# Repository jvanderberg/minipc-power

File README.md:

# minipc-power

Small power board for MCU-based emulator builds (Pico / ESP32 class with a 12 V 5" LCD). Runs from USB-C or a 1S2P
18650 pack, charges the pack whenever USB-C is plugged in, and supplies 12 V, 5 V and 3.3 V.

## Features

- **USB-C PD input:** requests 9 V (CH224Q), falls back to 5 V on non-PD chargers; TVS on VBUS.
- **Charger:** BQ25606 standalone switching charger, 1.44 A charge to 4.2 V, 1.9 A input limit. Power path: the
  board runs from USB even with a dead or missing pack. NTC input for charge-temperature limits.
- **Battery protection** for bare cells: HY2113 protector (over-charge 4.28 V, over-discharge 2.80 V, over-current,
  short circuit), 10 A fuse, reverse-polarity FET.
- **Outputs**, all switched together by one on/off switch (off by default):
  - **12 V, 0.5 A:** TPS61178 synchronous boost with output disconnect (for the LCD)
  - **5 V, 2.5 A:** TPS61088-Q1 synchronous boost with a soft-start load switch
  - **3.3 V, 1.5 A:** TPS63802 buck-boost (regulated across the whole battery range)
- **Power budget:** 15 W combined as a peak; about 10-12 W continuous in a closed box (see `docs/thermal.md`).
- **Solder pads** for everything: battery, outputs, on/off switch, NTC, status (charging, power good, 3.3 V good,
  battery voltage sense).
- **Board:** 52 x 36 mm, 4 layers (JLCPCB JLC04161H-7628), parts from LCSC; every part has its datasheet link.

## Status

Design reviewed, not yet built. Bench checks to run first: `docs/power-design.md` s9 and `docs/review-2026-10-24.md`.
`hardware/production/` predates the latest board changes: regenerate it before ordering.

## Files

- `hardware/` - KiCad 10 project (schematic, board, symbols, footprints, 3D models)
- `tools/` - the schematic and board are generated by these scripts; edit them, not the KiCad files:
  `python3 tools/gen_schematic.py && bash tools/build_board.sh` (needs KiCad 10 and
  [kicad-skills](https://github.com/jvanderberg/kicad-skills))
- `docs/requirements.md` - requirements and architecture (start here)
- `docs/power-design.md` - every component value and where it comes from
- `docs/thermal.md` - heat budget
- `docs/review-2026-10-24.md` - design review: fixed, open, owner decisions, bench checks
- `docs/layout-compliance.md` - each converter's layout against its datasheet
- `docs/skill-gaps.md` - problems found in the kicad-skills plugin while designing this board

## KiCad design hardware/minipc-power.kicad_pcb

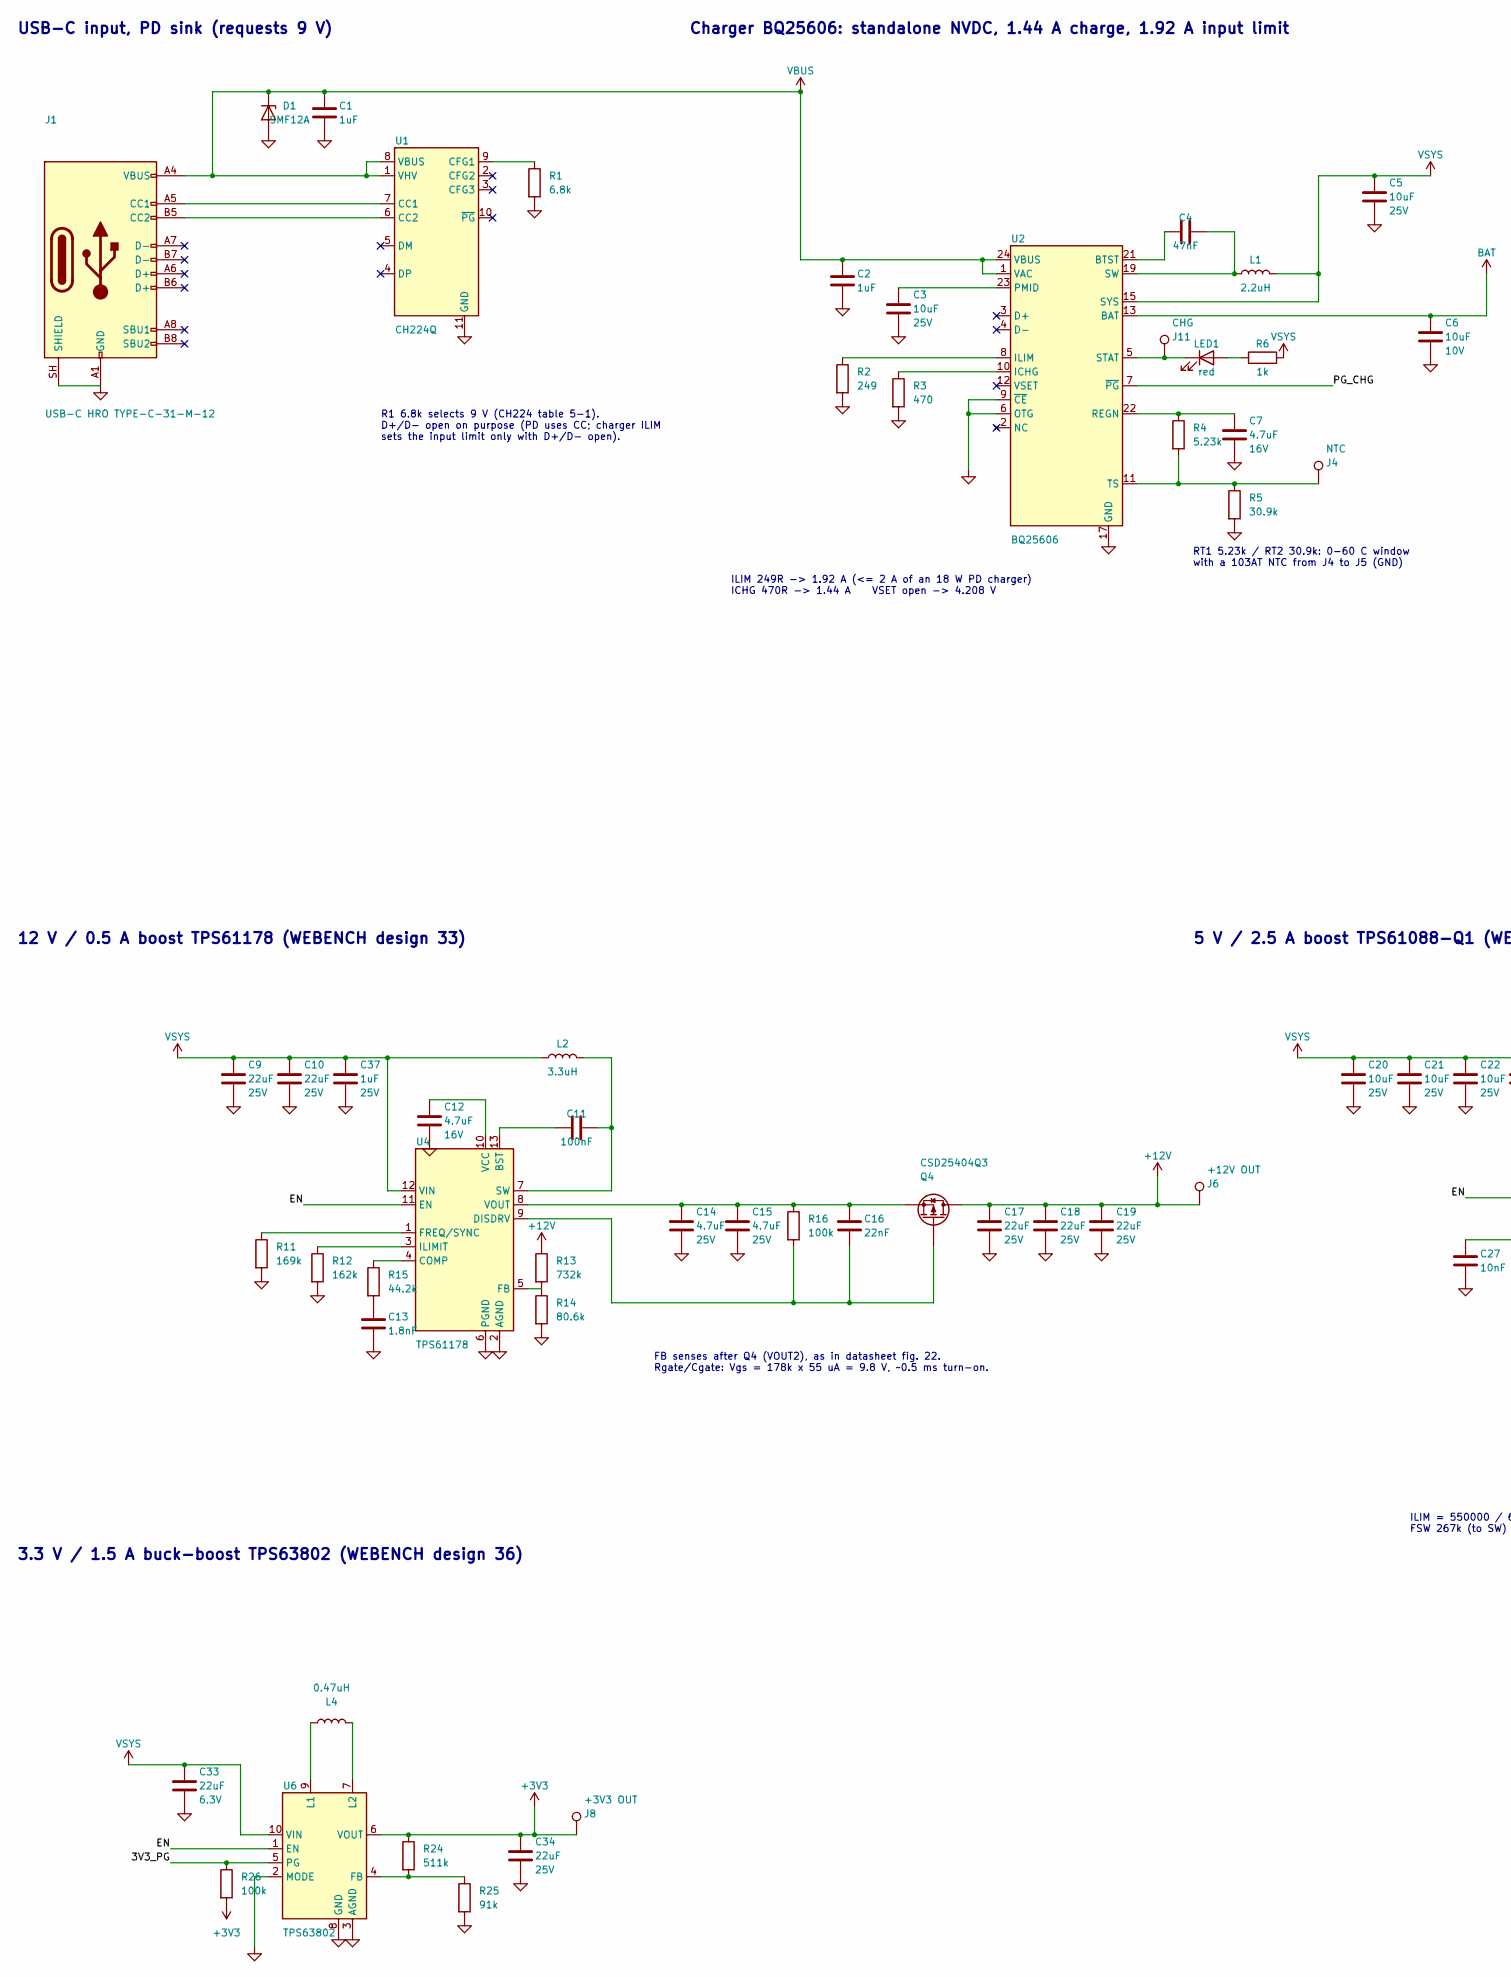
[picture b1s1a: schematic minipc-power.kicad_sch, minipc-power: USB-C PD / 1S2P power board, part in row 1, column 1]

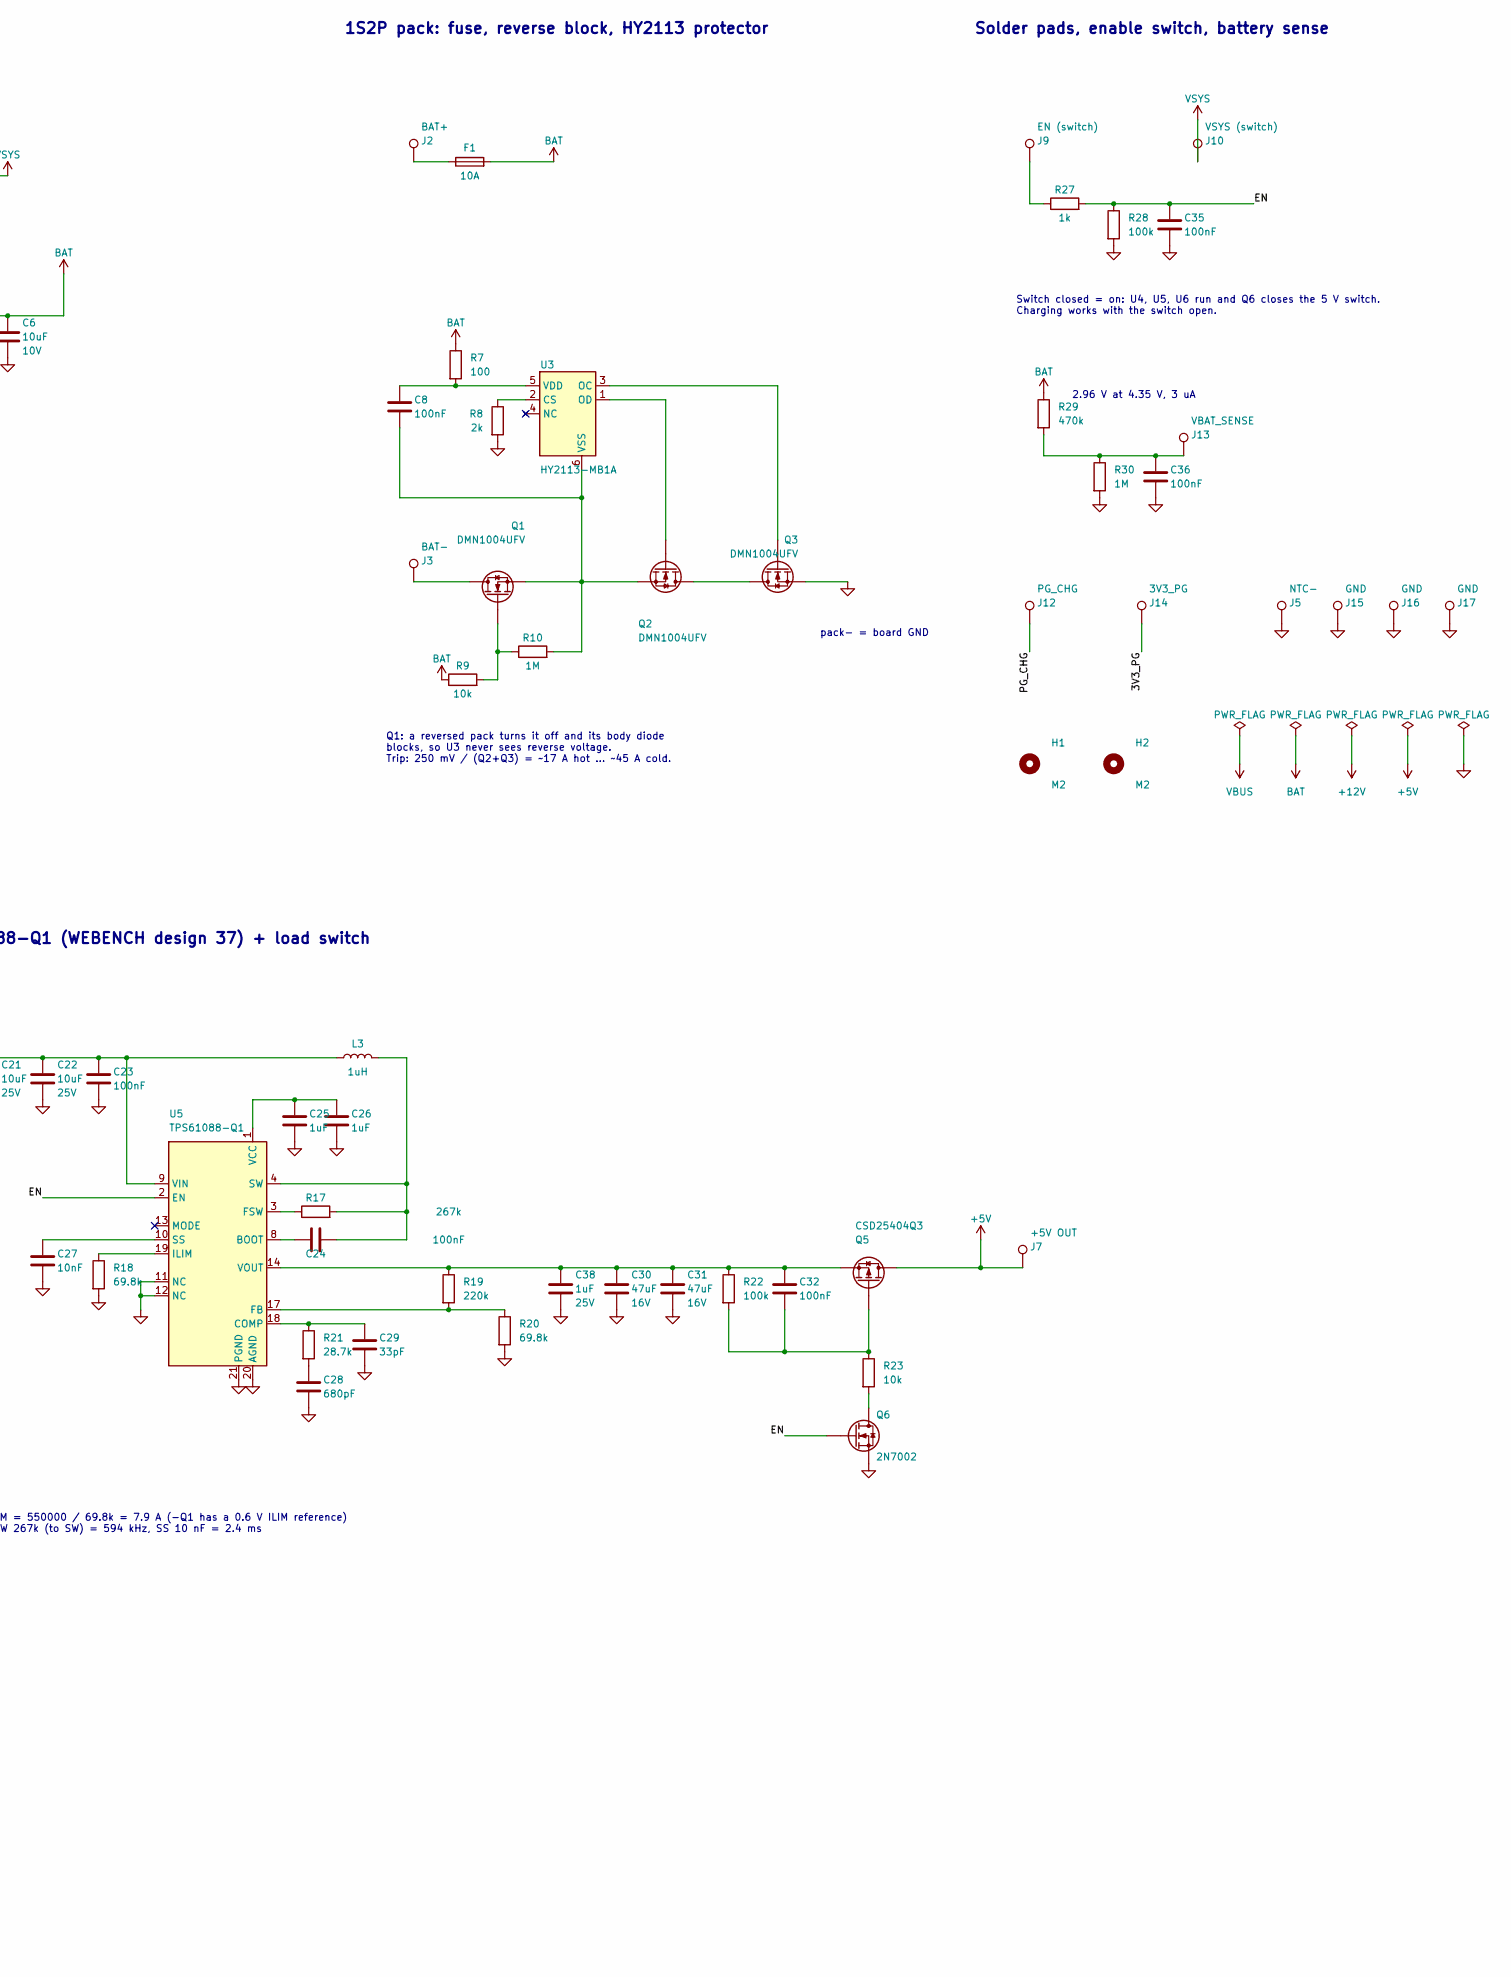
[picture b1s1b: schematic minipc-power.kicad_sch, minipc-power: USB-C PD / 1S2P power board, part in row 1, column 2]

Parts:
C1, C2, C25, C26: 1uF; C_0603_1608Metric; LCSC C15849
C3, C5, C20, C21, C22: 10uF; C_0805_2012Metric; Voltage 25V; LCSC C15850
C4: 47nF; C_0402_1005Metric; LCSC C307434
C6: 10uF; C_0603_1608Metric; Voltage 10V; LCSC C19702
C7, C12: 4.7uF; C_0603_1608Metric; Voltage 16V; LCSC C19666
C8, C11, C23, C24, C32, C35, C36: 100nF; C_0402_1005Metric; LCSC C1525
C9, C10, C34: 22uF; C_0805_2012Metric; Voltage 25V; LCSC C45783
C13: 1.8nF; C_0402_1005Metric; LCSC C107024
C14, C15: 4.7uF; C_0805_2012Metric; Voltage 25V; LCSC C1779
C16: 22nF; C_0402_1005Metric; LCSC C337699
C17, C18, C19: 22uF; C_1210_3225Metric; Voltage 25V; LCSC C52306
C27: 10nF; C_0402_1005Metric; LCSC C15195
C28: 680pF; C_0402_1005Metric; LCSC C307451
C29: 33pF; C_0402_1005Metric; LCSC C70465
C30, C31: 47uF; C_1210_3225Metric; Voltage 16V; LCSC C77101
C33: 22uF; C_0603_1608Metric; Voltage 6.3V; LCSC C59461
C37, C38: 1uF; C_0402_1005Metric; Voltage 25V; LCSC C52923
D1: SMF12A; D_SOD-123F; LCSC C123800
F1: 10A; Fuse_Littelfuse-NANO2-451_453; LCSC C44479
H1, H2: M2; MountingHole_2.2mm_M2
J1: USB-C HRO TYPE-C-31-M-12; USB_C_Receptacle_HRO_TYPE-C-31-M-12; LCSC C165948
J2: BAT+; TestPoint_THTPad_2.5x2.5mm_Drill1.2mm
J3: BAT-; TestPoint_THTPad_D2.5mm_Drill1.2mm
J4: NTC; TestPoint_THTPad_2.0x2.0mm_Drill1.0mm
J5: NTC-; TestPoint_THTPad_D2.0mm_Drill1.0mm
J6: +12V OUT; TestPoint_THTPad_2.5x2.5mm_Drill1.2mm
J7: +5V OUT; TestPoint_THTPad_2.5x2.5mm_Drill1.2mm
J8: +3V3 OUT; TestPoint_THTPad_2.5x2.5mm_Drill1.2mm
J9: EN (switch); TestPoint_THTPad_2.0x2.0mm_Drill1.0mm
J10: VSYS (switch); TestPoint_THTPad_2.0x2.0mm_Drill1.0mm
J11: CHG; TestPoint_THTPad_2.0x2.0mm_Drill1.0mm
J12: PG_CHG; TestPoint_THTPad_2.0x2.0mm_Drill1.0mm
J13: VBAT_SENSE; TestPoint_THTPad_2.0x2.0mm_Drill1.0mm
J14: 3V3_PG; TestPoint_THTPad_2.0x2.0mm_Drill1.0mm
J15, J16, J17: GND; TestPoint_THTPad_D2.5mm_Drill1.2mm
L1: 2.2uH; FXL0630-2R2-M; LCSC C167218
L2: 3.3uH; FXL0630-3R3-M; LCSC C167219
L3: 1uH; FXL0630-1R0-M; LCSC C167216
L4: 0.47uH; FXL0530-R47-M; LCSC C475515
LED1: red; LED_0603_1608Metric; LCSC C2286
Q1, Q2, Q3: DMN1004UFV; Diodes_PowerDI3333-8; LCSC C316138
Q4, Q5: CSD25404Q3; VSON-8_3.3x3.3mm_P0.65mm_NexFET; LCSC C2865523
Q6: 2N7002; SOT-23; LCSC C8545
R1: 6.8k; R_0402_1005Metric; LCSC C25917
R2: 249; R_0402_1005Metric; LCSC C25096
R3: 470; R_0402_1005Metric; LCSC C25117
R4: 5.23k; R_0402_1005Metric; LCSC C25907
R5: 30.9k; R_0402_1005Metric; LCSC C270615
R6, R27: 1k; R_0402_1005Metric; LCSC C11702
R7: 100; R_0402_1005Metric; LCSC C25076
R8: 2k; R_0402_1005Metric; LCSC C4109
R9, R23: 10k; R_0402_1005Metric; LCSC C25744
R10, R30: 1M; R_0402_1005Metric; LCSC C26083
R11: 169k; R_0402_1005Metric; LCSC C25758
R12: 162k; R_0402_1005Metric; LCSC C54068
R13: 732k; R_0402_1005Metric; LCSC C27016
R14: 80.6k; R_0402_1005Metric; LCSC C25921
R15: 44.2k; R_0402_1005Metric; LCSC C25895
R16, R22, R26, R28: 100k; R_0402_1005Metric; LCSC C25741
R17: 267k; R_0402_1005Metric; LCSC C270622
R18, R20: 69.8k; R_0402_1005Metric; LCSC C26985
R19: 220k; R_0402_1005Metric; LCSC C25767
R21: 28.7k; R_0402_1005Metric; LCSC C26972
R24: 511k; R_0402_1005Metric; LCSC C64042
R25: 91k; R_0402_1005Metric; LCSC C144733
R29: 470k; R_0402_1005Metric; LCSC C25790
U1: CH224Q; CH224Q_C46061833; LCSC C46061833
U2: BQ25606; Texas_RGE0024H_VQFN-24-1EP_4x4mm_P0.5mm_EP2.7x2.7mm_Thermal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; LCSC C374063
U3: HY2113-MB1A; SOT-23-6; LCSC C168772
U4: TPS61178; TPS61178RNWR; LCSC C127918
U5: TPS61088-Q1; Texas_VQFN-RHL-20_ThermalVias; LCSC C1850341
U6: TPS63802; TPS63802DLAR; LCSC C2845237

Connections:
+3V3: C34.1, J8.1, R24.1, R26.2, U6.6 (VOUT)
+5V: J7.1, Q5.1 (D), Q5.2 (D), Q5.3 (D)
+12V: C17.1, C18.1, C19.1, J6.1, Q4.1 (D), Q4.2 (D), Q4.3 (D), R13.1
/3V3_PG: J14.1, R26.1, U6.5 (PG)
/EN: C35.1, Q6.1 (G), R27.2, R28.1, U4.11 (EN), U5.2 (EN), U6.1 (EN)
/PG_CHG: J12.1, U2.7 (~PG)
BAT: C6.1, F1.2, R7.1, R9.1, R29.1, U2.13 (BAT), U2.14 (BAT)
GND: C1.2, C2.2, C3.2, C5.2, C6.2, C7.2, C9.2, C10.2, C12.2, C13.2, C14.2, C15.2, C17.2, C18.2, C19.2, C20.2, C21.2, C22.2, C23.2, C25.2, C26.2, C27.2, C28.2, C29.2, C30.2, C31.2, C33.2, C34.2, C35.2, C36.2, C37.2, C38.2, D1.2 (A), J1.A1 (GND), J1.A12 (GND), J1.B1 (GND), J1.B12 (GND), J1.SH (SHIELD), J5.1, J15.1, J16.1, J17.1, Q3.1 (S), Q3.2 (S), Q3.3 (S), Q6.2 (S), R1.2, R2.2, R3.2, R5.2, R8.2, R11.2, R12.2, R14.2, R18.2, R20.2, R25.2, R28.2, R30.2, U1.11 (GND), U2.6 (OTG), U2.9 (~CE), U2.17 (GND), U2.18 (GND), U2.25 (GND), U4.2 (AGND), U4.6 (PGND), U5.11 (NC), U5.12 (NC), U5.20 (AGND), U5.21 (PGND), U6.2 (MODE), U6.3 (AGND), U6.8 (GND)
unnamed: C4.2, L1.1, U2.19 (SW), U2.20 (SW)
unnamed: C13.1, R15.2
unnamed: C24.2, L3.2, R17.2, U5.4 (SW), U5.5 (SW), U5.6 (SW), U5.7 (SW)
unnamed: C28.1, R21.2
unnamed: C36.1, J13.1, R29.2, R30.1
unnamed: F1.1, J2.1
unnamed: J1.A5 (CC1), U1.7 (CC1)
unnamed: J1.B5 (CC2), U1.6 (CC2)
unnamed: J9.1, R27.1
unnamed: LED1.2 (A), R6.1
unnamed: J11.1, LED1.1 (K), U2.5 (STAT)
unnamed: J3.1, Q1.5 (D)
unnamed: Q1.4 (G), R9.2, R10.1
unnamed: Q2.5 (D), Q3.5 (D)
unnamed: Q2.4 (G), U3.1 (OD)
unnamed: Q3.4 (G), U3.3 (OC)
unnamed: C16.2, Q4.4 (G), R16.2, U4.9 (DISDRV)
unnamed: C14.1, C15.1, C16.1, Q4.5 (S), R16.1, U4.8 (VOUT)
unnamed: C32.2, Q5.4 (G), R22.2, R23.1
unnamed: C30.1, C31.1, C32.1, C38.1, Q5.5 (S), R19.1, R22.1, U5.14 (VOUT), U5.15 (VOUT), U5.16 (VOUT)
unnamed: Q6.3 (D), R23.2
unnamed: R1.1, U1.9 (CFG1)
unnamed: C4.1, U2.21 (BTST)
unnamed: R3.1, U2.10 (ICHG)
unnamed: R2.1, U2.8 (ILIM)
unnamed: C3.1, U2.23 (PMID)
unnamed: C7.1, R4.1, U2.22 (REGN)
unnamed: J4.1, R4.2, R5.1, U2.11 (TS)
unnamed: R8.1, U3.2 (CS)
unnamed: C8.1, R7.2, U3.5 (VDD)
unnamed: C8.2, Q1.1 (S), Q1.2 (S), Q1.3 (S), Q2.1 (S), Q2.2 (S), Q2.3 (S), R10.2, U3.6 (VSS)
unnamed: C11.1, U4.13 (BST)
unnamed: R15.1, U4.4 (COMP)
unnamed: R13.2, R14.1, U4.5 (FB)
unnamed: R11.1, U4.1 (FREQ/SYNC)
unnamed: R12.1, U4.3 (ILIMIT)
unnamed: C11.2, L2.2, U4.7 (SW)
unnamed: C12.1, U4.10 (VCC)
unnamed: C24.1, U5.8 (BOOT)
unnamed: C29.1, R21.1, U5.18 (COMP)
unnamed: R19.2, R20.1, U5.17 (FB)
unnamed: R17.1, U5.3 (FSW)
unnamed: R18.1, U5.19 (ILIM)
unnamed: C27.1, U5.10 (SS)
unnamed: C25.1, C26.1, U5.1 (VCC)
unnamed: R24.2, R25.1, U6.4 (FB)
unnamed: L4.1, U6.9 (L1)
unnamed: L4.2, U6.7 (L2)
VBUS: C1.1, C2.1, D1.1 (K), J1.A4 (VBUS), J1.A9 (VBUS), J1.B4 (VBUS), J1.B9 (VBUS), U1.1 (VHV), U1.8 (VBUS), U2.1 (VAC), U2.24 (VBUS)
VSYS: C5.1, C9.1, C10.1, C20.1, C21.1, C22.1, C23.1, C33.1, C37.1, J10.1, L1.2, L2.1, L3.1, R6.2, U2.15 (SYS), U2.16 (SYS), U4.12 (VIN), U5.9 (VIN), U6.10 (VIN)

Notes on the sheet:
USB-C input, PD sink (requests 9 V)
R1 6.8k selects 9 V (CH224 table 5-1). D+/D- open on purpose (PD uses CC; charger ILIM sets the input limit only with D+/D- open).
Charger BQ25606: standalone NVDC, 1.44 A charge, 1.92 A input limit
ILIM 249R -> 1.92 A (<= 2 A of an 18 W PD charger) ICHG 470R -> 1.44 A VSET open -> 4.208 V
RT1 5.23k / RT2 30.9k: 0-60 C window with a 103AT NTC from J4 to J5 (GND)
1S2P pack: fuse, reverse block, HY2113 protector
pack- = board GND
Q1: a reversed pack turns it off and its body diode blocks, so U3 never sees reverse voltage. Trip: 250 mV / (Q2+Q3) = ~17 A hot ... ~45 A cold.
Solder pads, enable switch, battery sense
Switch closed = on: U4, U5, U6 run and Q6 closes the 5 V switch. Charging works with the switch open.
2.96 V at 4.35 V, 3 uA
12 V / 0.5 A boost TPS61178 (WEBENCH design 33)
FB senses after Q4 (VOUT2), as in datasheet fig. 22. Rgate/Cgate: Vgs = 178k x 55 uA = 9.8 V, ~0.5 ms turn-on.
5 V / 2.5 A boost TPS61088-Q1 (WEBENCH design 37) + load switch
ILIM = 550000 / 69.8k = 7.9 A (-Q1 has a 0.6 V ILIM reference) FSW 267k (to SW) = 594 kHz, SS 10 nF = 2.4 ms
3.3 V / 1.5 A buck-boost TPS63802 (WEBENCH design 36)

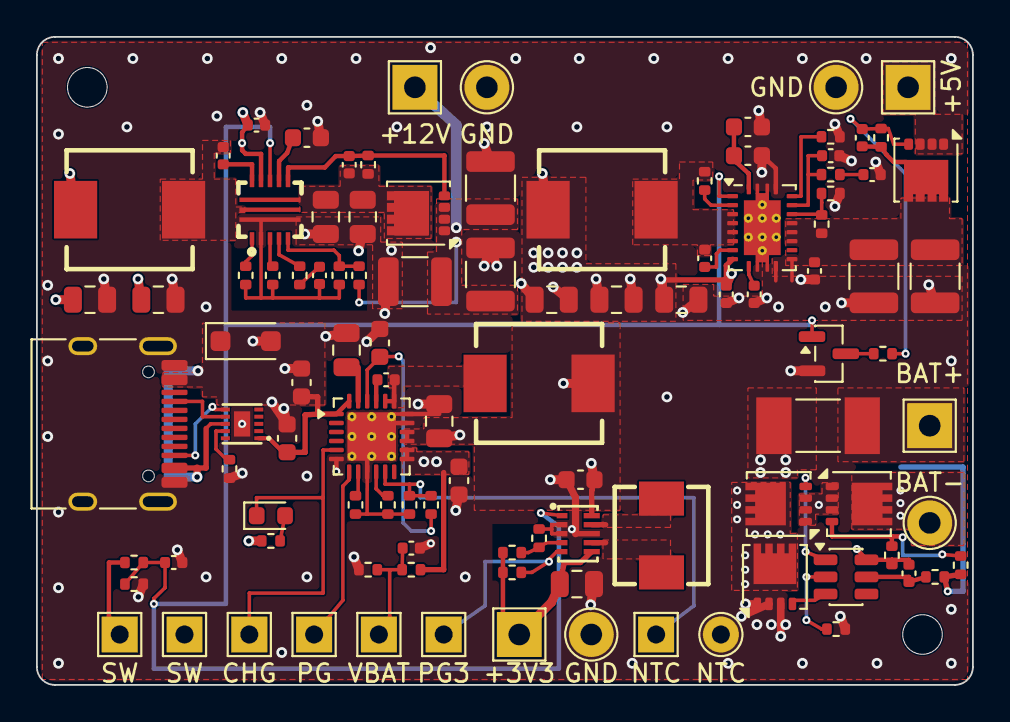
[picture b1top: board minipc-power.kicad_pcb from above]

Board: 4 copper layers, 52.0 x 36.0 mm, 106 parts (0 on the bottom side), 58 nets.

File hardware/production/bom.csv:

Designator,Footprint,Quantity,Value,LCSC Part #
"C1, C2, C25, C26",0603,4,1uF,C15849
"C10, C34, C9",0805,3,22uF,C45783
"C11, C23, C24, C32, C35, C36, C8",0402,7,100nF,C1525
"C12, C7",0603,2,4.7uF,C19666
C13,0402,1,1.8nF,C107024
"C14, C15",0805,2,4.7uF,C1779
C16,0402,1,22nF,C337699
"C17, C18, C19",1210,3,22uF,C52306
"C20, C21, C22, C3, C5",0805,5,10uF,C15850
C27,0402,1,10nF,C15195
C28,0402,1,680pF,C307451
C29,0402,1,33pF,C70465
"C30, C31",1210,2,47uF,C77101
C33,0603,1,22uF,C59461
"C37, C38",0402,2,1uF,C52923
C4,0402,1,47nF,C307434
C6,0603,1,10uF,C19702
D1,D_SOD-123F,1,SMF12A,C123800
F1,Fuse_Littelfuse-NANO2-451_453,1,10A,C44479
J1,USB_C_Receptacle_HRO_TYPE-C-31-M-12,1,USB-C HRO TYPE-C-31-M-12,C165948
L1,FXL0630-2R2-M,1,2.2uH,C167218
L2,FXL0630-3R3-M,1,3.3uH,C167219
L3,FXL0630-1R0-M,1,1uH,C167216
L4,FXL0530-R47-M,1,0.47uH,C475515
LED1,0603,1,red,C2286
"Q1, Q2, Q3",Texas_DQK,3,CSD13202Q2,C187839
"Q4, Q5",VSON-8_3.3x3.3mm_P0.65mm_NexFET,2,CSD25404Q3,C2865523
Q6,SOT-23,1,2N7002,C8545
R1,0402,1,6.8k,C25917
"R10, R30",0402,2,1M,C26083
R11,0402,1,169k,C25758
R12,0402,1,162k,C54068
R13,0402,1,732k,C27016
R14,0402,1,80.6k,C25921
R15,0402,1,44.2k,C25895
"R16, R22, R26, R28",0402,4,100k,C25741
R17,0402,1,267k,C270622
"R18, R20",0402,2,69.8k,C26985
R19,0402,1,220k,C25767
R2,0402,1,249,C25096
R21,0402,1,28.7k,C26972
"R23, R9",0402,2,10k,C25744
R24,0402,1,511k,C64042
R25,0402,1,91k,C144733
"R27, R6",0402,2,1k,C11702
R29,0402,1,470k,C25790
R3,0402,1,470,C25117
R4,0402,1,5.23k,C25907
R5,0402,1,30.9k,C270615
R7,0402,1,100,C25076
R8,0402,1,2k,C4109
U1,CH224Q_C46061833,1,CH224Q,C46061833
U2,Texas_RGE0024H_VQFN-24-1EP_4x4mm_P0.5mm_EP2.7x2.7mm_ThermalVias,1,BQ25606,C374063
U3,SOT-23-6,1,HY2113-MB1A,C168772
U4,TPS61178RNWR,1,TPS61178,C127918
U5,Texas_VQFN-RHL-20_ThermalVias,1,TPS61088-Q1,C1850341
U6,TPS63802DLAR,1,TPS63802,C2845237

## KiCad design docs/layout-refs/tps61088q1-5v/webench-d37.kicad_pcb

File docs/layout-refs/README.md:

# Layout references

Order of authority when they disagree:

1. **Datasheet Layout Guidelines and Layout Example** (`<part>/datasheet-layout.txt`, `datasheet-p*.png`). These win.
2. EVM user guide layout (not collected yet; the BQ25606 datasheet points to the BQ25601 EVM guide, PWR877).
3. **WEBENCH layouts** (`<part>/webench-d*.kicad_pcb`, imported from WEBENCH's EAGLE export with
   `kicad-cli pcb import --format eagle`). **Reference only**: they are EVM-style test boards with large pours, drawn
   around WEBENCH's own BOM (different inductor and capacitor sizes from our LCSC parts) and a generic stackup.
   They are useful for the arrangement right around each IC. `webench-raw/` holds the original downloads.

`tps61088-5v-commercial-REJECTED/` is the WEBENCH design for the discontinued commercial TPS61088; kept for the record,
do not use.

## Per-converter checklist (from the datasheets)

### BQ25606 charger (datasheet s12)
- Input cap at **PMID** and GND, shortest path (the buck's hot loop is PMID - HSFET - LSFET - GND).
- Inductor right at SW; SW copper as small as the charge current allows; **no parallel layers on SW**; keep SW away
  from other traces and planes.
- SYS/BAT output caps near the inductor and IC, grounds tied short to IC ground.
- Analog ground routed separately, joined to power ground **at the thermal pad only** (single point).
- REGN, BTST, VBUS decoupling caps at the pins.
- Thermal pad soldered, thermal vias under the IC to the inner ground planes.
- Via count/size sized for charge + system current.

### TPS61178 12 V boost (datasheet s11)
- Smallest loop: low-side FET (SW-PGND), rectifier FET (SW-VOUT), output cap.
- SW traces minimal; ground plane directly under the converter.
- Small ceramics closest to the IC, bulk further out.
- Wide VOUT/SW/GND copper with vias for heat.
- Input cap at VIN and PGND.
- FB and COMP network away from SW.
- Separate quiet ground trace for FB, COMP, FREQ and ILIMIT resistors, joined to power ground at one point.

### TPS61088-Q1 5 V boost (datasheet s11)
- SW traces minimal; ground plane under the regulator.
- Input cap at VIN and GND.
- Thermal pad to a large ground area with thermal vias ("high power density device").
- Example: bottom layer is a solid ground plane connected to the top-layer PGND and AGND areas by vias; AGND island
  for VCC/FSW/ILIM/COMP/FB parts.

### TPS63802 3.3 V buck-boost (datasheet s12)
- Input and output caps as close as possible, short wide traces.
- Power ground and control ground as separate nodes, joined near one of the IC's ground pins.
- Separate traces for power-stage supply and analog supply.
- FB trace away from the L1 and L2 nodes.

### CH224Q PD sink
- 3-page datasheet with no layout section: keep CC1/CC2 short to the connector, VHV/VBUS caps at the pins, ESD
  diodes at the connector.

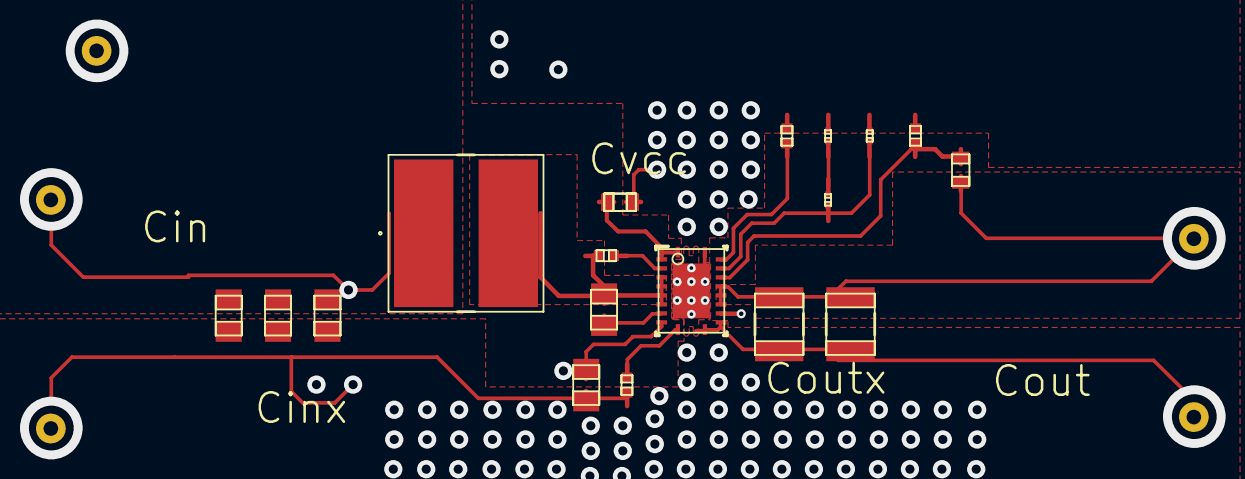
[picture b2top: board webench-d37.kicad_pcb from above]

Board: 10 copper layers, 24 parts (0 on the bottom side), 13 nets.

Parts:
Cbst0: 0805
Ccomp0, Ccomp2: 0201
Cin2: 0805
Cin_1, Cin_2, Cin_3: 0805
Cout_1, Cout_2: 1210_280
Css0: 0402
Cvcc_1, Cvcc_2: 0603
GND0, GND1: TP-1502
L1: VLP8040
MODE0: TP-1502
Rcomp0: 0201
Rfbb0: 0402
Rfbt0: 0603
Rlim0: 0402
Rt0: 0402
U1: RHL0020A
VIN0: TP-1502
VOUT0: TP-1502

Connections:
0: Ccomp0.2, Ccomp2.2, Cin2.2, Cin_1.2, Cin_2.2, Cin_3.2, Cout_1.2, Cout_2.2, Css0.2, Cvcc_1.2, Cvcc_2.2, GND0.1, GND1.1, Rfbb0.2, Rlim0.2, U1.11, U1.12, U1.20, U1.21
2: Cin2.1, Cin_1.1, Cin_2.1, Cin_3.1, L1.1, U1.9, VIN0.1
3: Ccomp0.1, Rcomp0.2
4: Cvcc_1.1, Cvcc_2.1, U1.1, U1.2
5: Ccomp2.1, Rcomp0.1, U1.18
9: Cout_1.1, Cout_2.1, Rfbt0.1, U1.14, U1.15, U1.16, VOUT0.1
11: Rfbb0.1, Rfbt0.2, U1.17
12: Cbst0.1, L1.2, Rt0.1, U1.4, U1.5, U1.6, U1.7
14: Rlim0.1, U1.19
15: Rt0.2, U1.3
17: MODE0.1, U1.13
19: Css0.1, U1.10
21: Cbst0.2, U1.8

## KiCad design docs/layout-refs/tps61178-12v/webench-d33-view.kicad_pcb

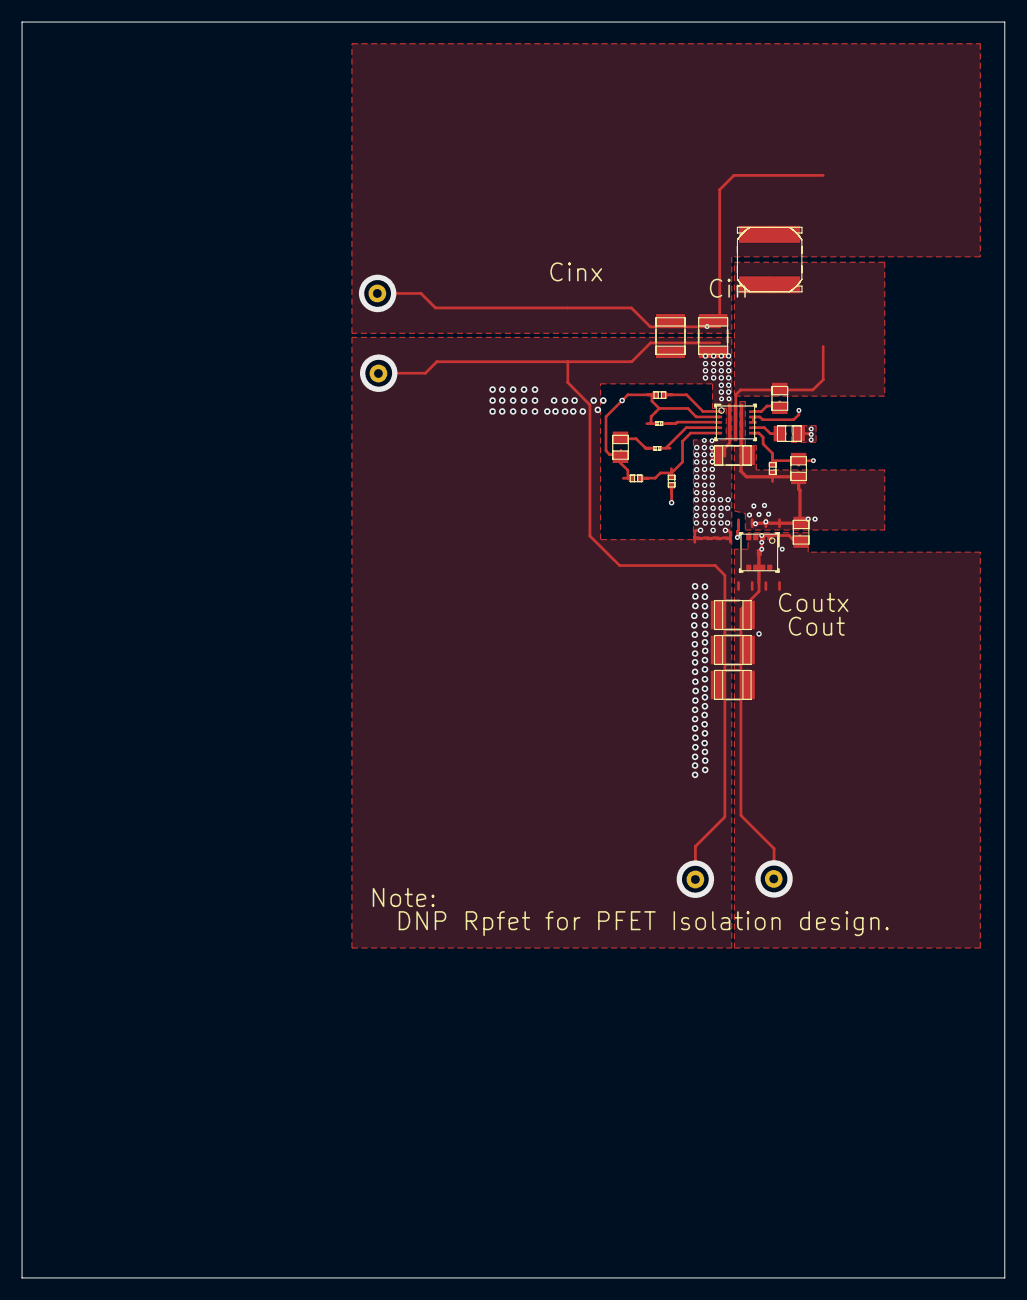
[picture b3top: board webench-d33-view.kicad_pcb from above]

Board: 10 copper layers, 91.4 x 116.8 mm, 24 parts (0 on the bottom side), 13 nets.

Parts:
Cboot0: 0805
Ccomp0: 0805
Cgate0: 0805
Cin_1, Cin_2: 1210
Cout1: 1206
Cout_1, Cout_2, Cout_3: 1210
Cvcc0: 0805
GND0, GND1: TP-1502
L1: DG6045C
M3: DQG0008A
Rcomp0: 0201
Rfbb0: 0402
Rfbt0: 0402
Rgate0: 0402
Rilim0: 0201
Rpfet0: 0805
Rt0: 0402
U1: RNW0013A
VIN0: TP-1502
VOUT0: TP-1502

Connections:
0: Cboot0.2, U1.13
1: Cgate0.2, Rgate0.2, U1.9
2: Cgate0.1, Cout1.1, Rgate0.1, Rpfet0.1, U1.8
5: Rt0.1, U1.1
8: Cin_1.1, Cin_2.1, L1.2, U1.11, U1.12, VIN0.1
10: Cboot0.1, L1.1, U1.7
11: Rfbb0.1, Rfbt0.2, U1.5
13: Cout_1.1, Cout_2.1, Cout_3.1, M3.1, M3.2, M3.3, M3.4, M3.5, M3.6, M3.7, M3.8, M3.9, Rfbt0.1, Rpfet0.2, VOUT0.1
14: Ccomp0.1, Rcomp0.2
18: Ccomp0.2, Cin_1.2, Cin_2.2, Cout1.2, Cout_1.2, Cout_2.2, Cout_3.2, Cvcc0.2, GND0.1, GND1.1, Rfbb0.2, Rilim0.2, Rt0.2, U1.2, U1.6
19: Cvcc0.1, U1.10
24: Rcomp0.1, U1.4
27: Rilim0.1, U1.3

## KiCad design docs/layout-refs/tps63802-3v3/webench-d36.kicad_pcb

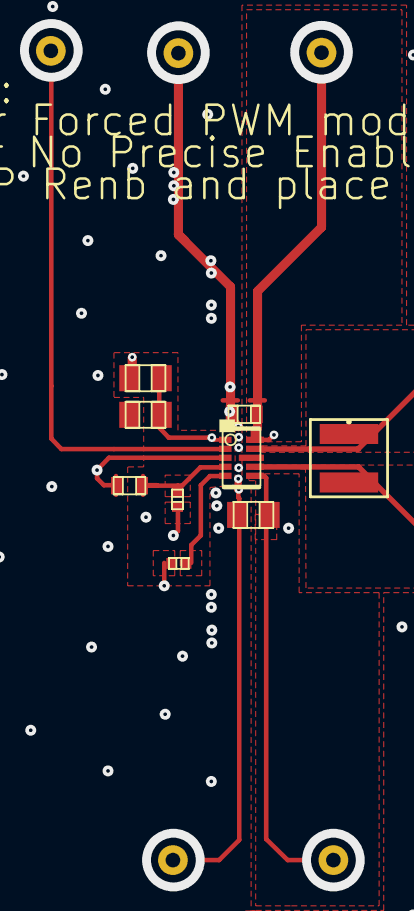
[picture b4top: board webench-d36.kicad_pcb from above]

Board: 10 copper layers, 14 parts (0 on the bottom side), 8 nets.

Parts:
Cin0: 0603
Cout0: 0805
GND0, GND1: TP-1502
L1: XFL4015
MODE0: TP-1502
Renb0: 0805
Rent0: 0805
Rfbb0: 0603
Rfbt0: 0402
Rpg0: 0402
U1: DLA0010A
VIN0: TP-1502
VOUT0: TP-1502

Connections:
0: Cin0.2, Cout0.2, GND0.1, GND1.1, Renb0.2, Rfbb0.2, U1.3, U1.8
2: Cin0.1, Renb0.1, Rent0.1, Rent0.2, U1.1, U1.10, VIN0.1
5: Rfbb0.1, Rfbt0.2, U1.4
7: Cout0.1, Rfbt0.1, Rpg0.1, U1.6, VOUT0.1
9: L1.2, U1.7
10: Rpg0.2, U1.5
11: MODE0.1, U1.2
13: L1.1, U1.9
